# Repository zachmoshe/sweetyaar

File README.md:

# SweetYaar

SweetYaar is an ESP32-WROOM-32 baby toy audio controller. The current codebase
is a PlatformIO/Arduino C++ firmware project with:

- Bluetooth Classic A2DP speaker support.
- BLE parent controls and settings over a single-page Web Bluetooth app.
- SD-card WAV playback for songs and animal sounds.
- Configurable content metadata, sleep-mode behavior, and Bedtime mode.
- Hardware planning notes for the prototype and final PCB.

## Repository History

This repository has three useful history points:

- `main`: the current ESP32/PlatformIO firmware, Web Bluetooth parent remote,
  SD-card content template, sleep-mode work, and hardware planning artifacts.
- `v1.0`: the previous MicroPython-era implementation that used to be the
  remote `main` branch.
- `v0.0`: an older educational snapshot that used to be named `v1.0`.

To inspect the previous implementation:

```bash
git fetch origin
git switch v1.0
```

To inspect the older educational snapshot:

```bash
git switch v0.0
```

To return to the current codebase:

```bash
git switch main
```

## Development Setup

Create or refresh the root development environment:

```bash
make setup
```

The root `Makefile` is the common entry point for project tasks. Run `make help`
to list every command. The most common ones are:

```bash
make app            # Serve the parent app at http://localhost:8000/
make build          # Build the complete ESP32 firmware
make flash          # Build and upload to a connected ESP32
make monitor        # Open the serial monitor
make flash-monitor  # Flash, then monitor
make test           # Run the full regression suite
make test-unit      # Host-only tests; never flashes or touches hardware
make test-device    # Approved real-device tests (see tests/README.md)
```

Targets are intentionally thin wrappers around the component tools and can be
extended in `Makefile`. Variables can be overridden per invocation, for example
`make app APP_PORT=8080` or
`make monitor SERIAL_PORT=/dev/cu.SLAB_USBtoUART`.

## Regression Tests

Run the standard regression suite:

```bash
make test
```

The `dev` dependency group is installed by default and locked in `uv.lock`. If
the venv is activated, plain `python -m pytest` is equivalent.

See [`docs/engineering/firmware.md`](docs/engineering/firmware.md) for firmware behavior, architecture,
build instructions, and test coverage.

## Project Layout

- `firmware/esp32/`: PlatformIO project and production firmware source.
- `hardware/mainboard/`: production KiCad mainboard project and manufacturing exports.
- `hardware/debugger/`: KiCad project for the separate USB-UART debugger board.
- `hardware/libraries/`: repository-owned KiCad symbols, footprints, and 3D models.
- `hardware/mechanical/enclosure/`: enclosure STL models.
- `hardware/references/`: hardware datasheet and application-note index.
- `tests/`: host-side pytest, native C++, app, and firmware-build regression tests.
- `app/`: the deployable Web Bluetooth parent remote and editable design assets.
- `docs/engineering/`: firmware, app, and hardware engineering guides.
- `docs/assets/`: shared engineering-documentation images and diagrams.
- `content/sd-card-template/`: expected SD-card folder structure, metadata, and config.
- `tools/`: standalone utilities, including the opt-in device test runner and the WAV mono converter.
- [`docs/overview.md`](docs/overview.md): high-level project overview and design history.
- [`docs/engineering/firmware.md`](docs/engineering/firmware.md): device behavior, firmware components,
  build instructions, and regression tests.
- [`docs/engineering/mobile-app.md`](docs/engineering/mobile-app.md): parent remote behavior, design
  assets, Bedtime mode, offline support, deployment, and app tests.
- [`docs/engineering/hardware.md`](docs/engineering/hardware.md): system architecture, DevKit wiring,
  production power design, safety requirements, and bring-up checks.

## Hardware Target

The firmware targets the original ESP32-WROOM-32. This matters because the toy
uses Bluetooth Classic A2DP, which is not available on ESP32-S3/C3/C6 variants.

The current hardware plan uses GPIO13/`PERIPH_PWR_EN` as the shared active-HIGH
enable for the 3.3 V peripheral load switch and the 5 V peripheral boost. The
real app enables both branches during boot, then drives and RTC-holds GPIO13 LOW
before deep sleep; see
[`docs/engineering/hardware.md`](docs/engineering/hardware.md) for the AP2281-3WG-7 SD switch, 5 V amp
boost, required common ground, and shared-enable pulldown.

The production status indicator is a single **WS2812B-V6 (LCSC C52917433)**,
a 5050 SMD addressable RGB LED on `5V_PERIPH_SW`. GPIO2 drives `DIN` directly
through the 330 Ω `R_LED_DIN1` series resistor (LCSC C23138); the LED interface
has no MMBT3904 stage or 5 V pull-up. The `sweetyaar` environment explicitly
selects non-inverted RMT output (`SWEETYAAR_STATUS_LED_DATA_INVERTED=0`) and
24-bit GRB data (`SWEETYAAR_STATUS_LED_RGBW=0`,
`SWEETYAAR_STATUS_LED_COLOR_ORDER_GRB=1`). The `sweetyaar-generic` environment
retains the directly wired 32-bit RGBW/SK6812-style bench LED with non-inverted
data and GRBW channel order. GPIO16 and GPIO17 carry BQ25186 charger I2C SDA
and SCL, respectively. A controller-wide brightness setting scales every
available color channel and currently defaults to 50% pending enclosure testing.

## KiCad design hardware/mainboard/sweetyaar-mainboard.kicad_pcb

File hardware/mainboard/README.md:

# SweetYaar mainboard

Create the production KiCad project in this directory. Keep the project,
schematic, PCB, project library tables, and board-specific design rules together:

- `sweetyaar-mainboard.kicad_pro`
- `sweetyaar-mainboard.kicad_sch`
- `sweetyaar-mainboard.kicad_pcb`

Store immutable fabrication and assembly snapshots under `releases/<revision>/`
when a board revision is actually sent for manufacturing. Generated working
outputs belong in an ignored `fab/` directory.

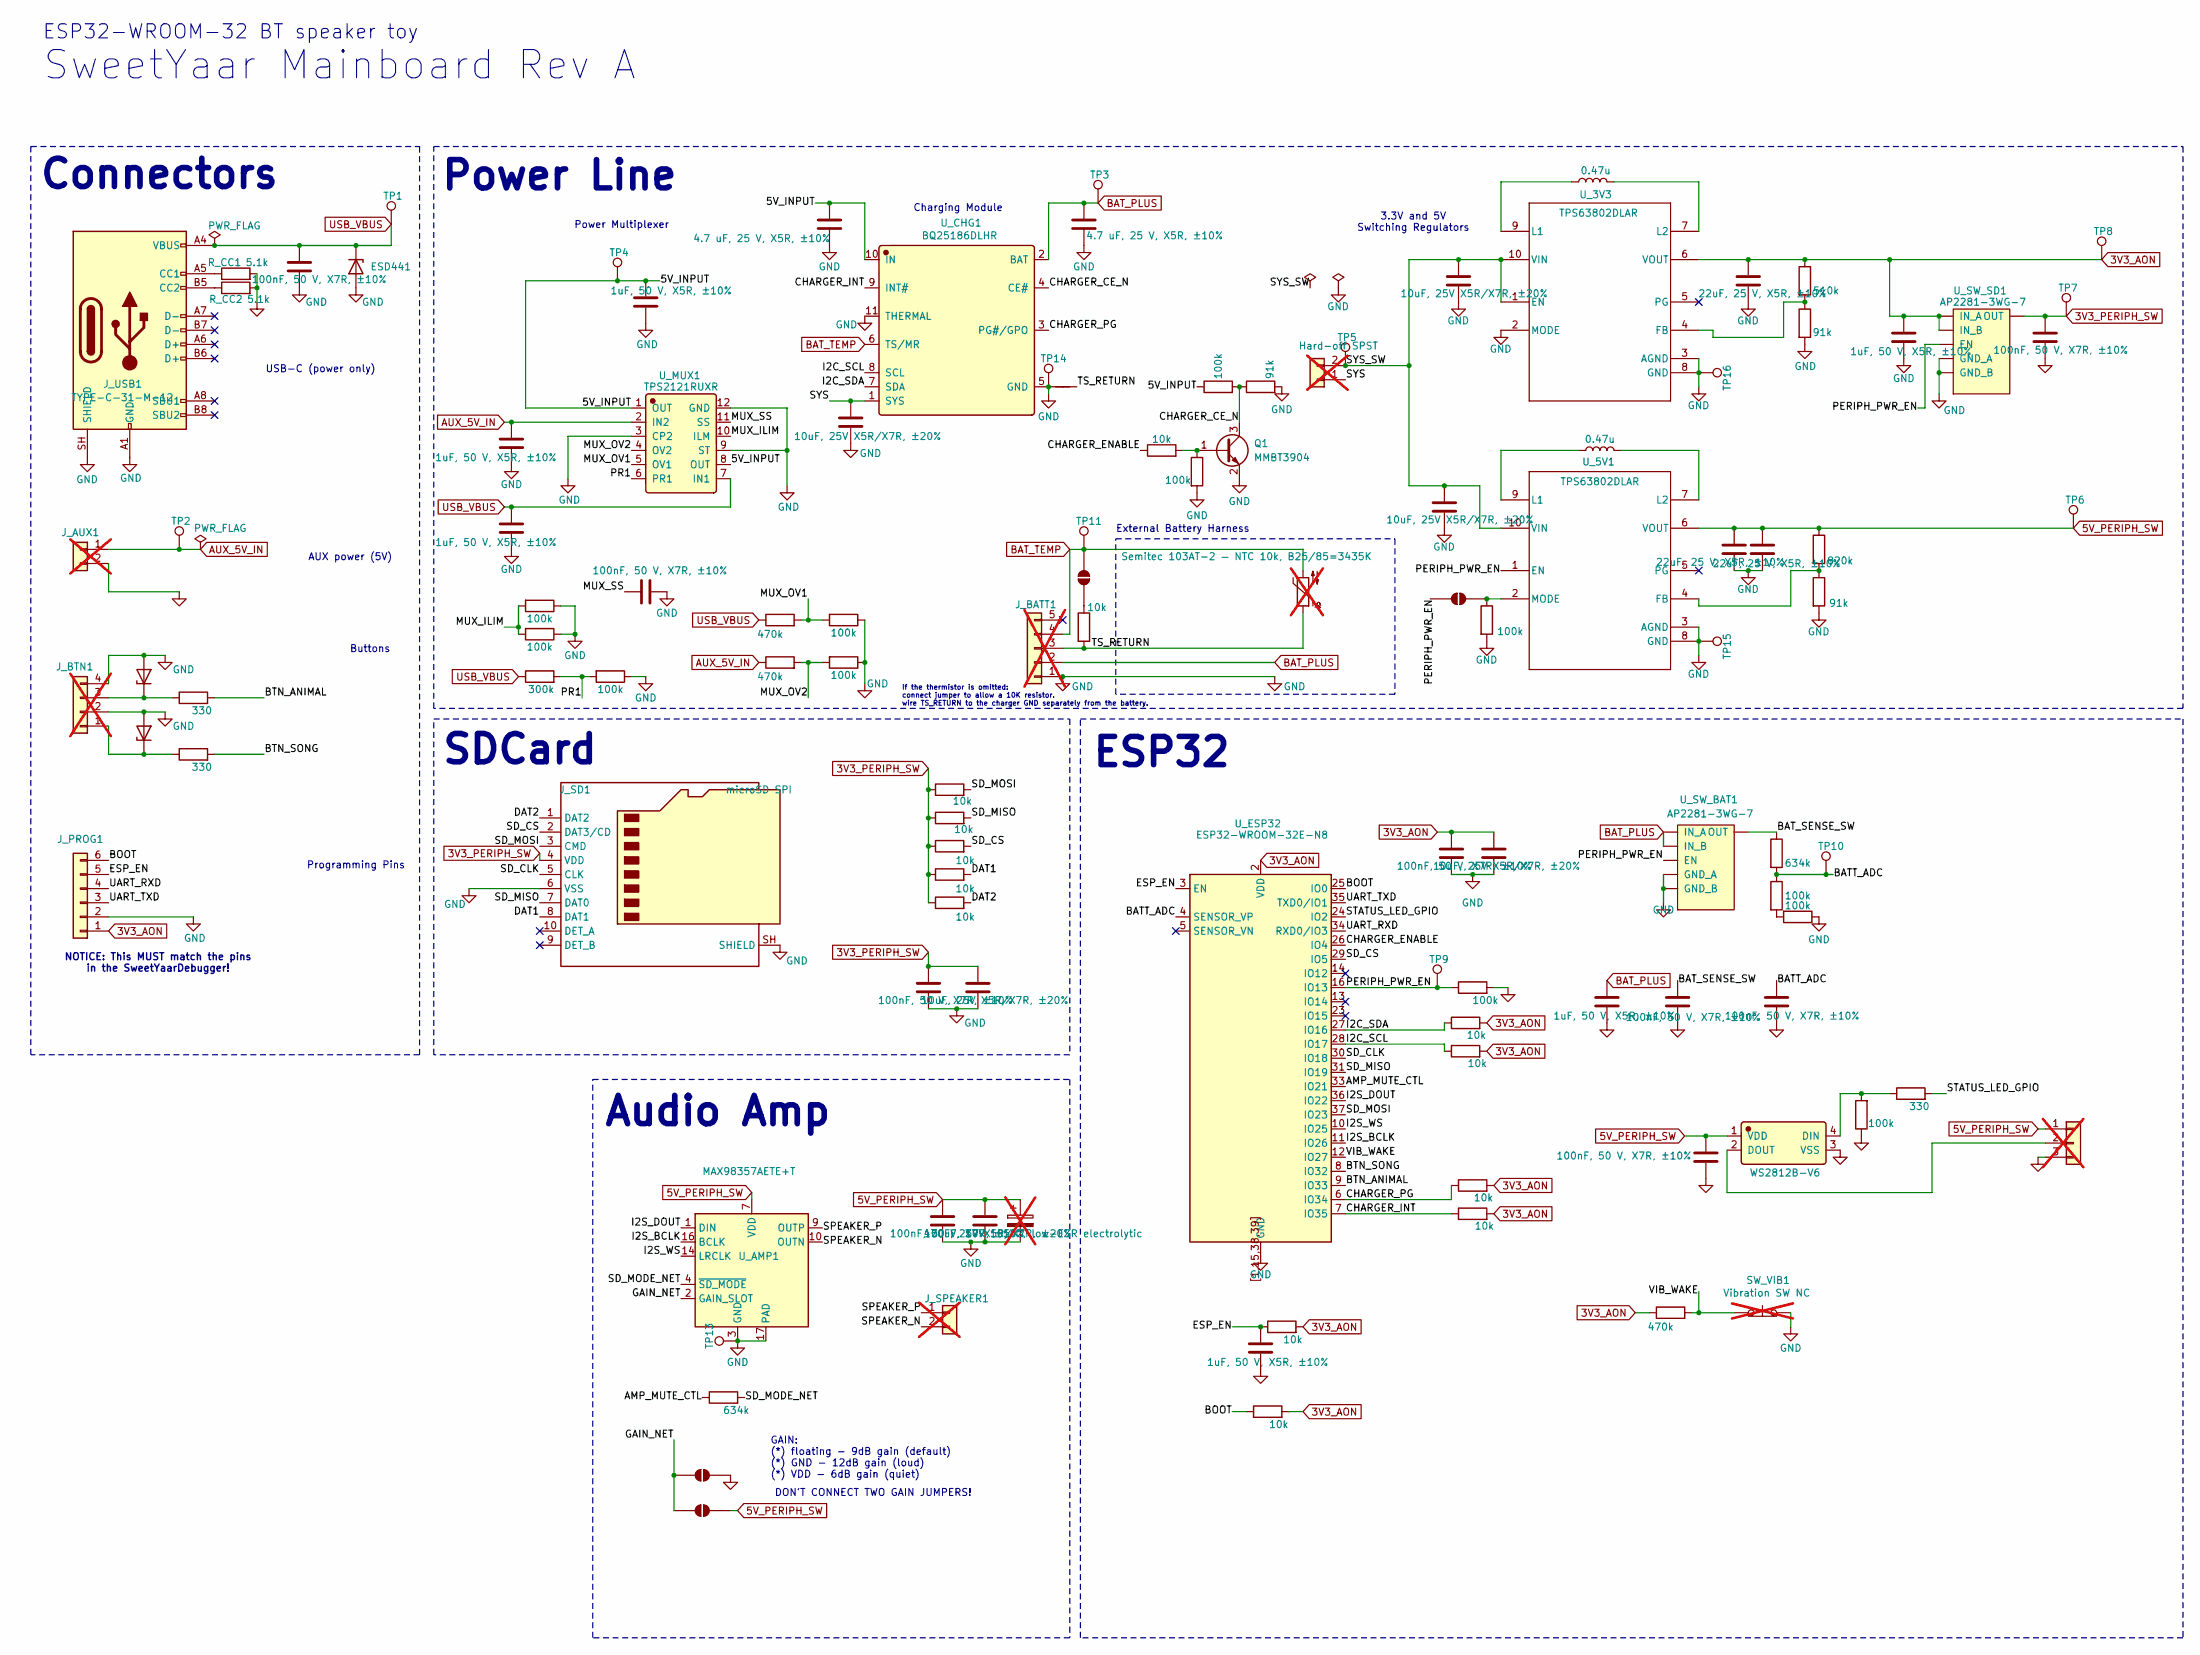
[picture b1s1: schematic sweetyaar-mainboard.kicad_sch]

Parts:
C1: 100nF, 50 V, X7R, ±10%; C_0603_1608Metric; LCSC C14663
C_3V3_IN1, C_5V_IN1: 10uF, 25V X5R/X7R, ±20%; C_0805_2012Metric; LCSC C15850
C_3V3_OUT1, C_5V_OUT1, C_5V_OUT2: 22uF, 25 V, X5R, ±10%; C_1206_3216Metric; LCSC C12891
C_AMP1: 100nF, 50 V, X7R, ±10%; C_0603_1608Metric; LCSC C14663
C_AMP2: 10uF, 25V X5R/X7R, ±20%; C_0805_2012Metric; LCSC C15850
C_AMP3: 470uF, 10V 105°C, low-ESR electrolytic; CP_Radial_D8.0mm_P3.50mm; LCSC C88765; not fitted
C_BAT_ADC1: 100nF, 50 V, X7R, ±10%; C_0603_1608Metric; LCSC C14663
C_BAT_SW_IN1: 1uF, 50 V, X5R, ±10%; C_0603_1608Metric; LCSC C15849
C_BAT_SW_OUT1: 100nF, 50 V, X7R, ±10%; C_0603_1608Metric; LCSC C14663
C_CHG_BAT1: 4.7 uF, 25 V, X5R, ±10%; C_0805_2012Metric; LCSC C1779
C_CHG_SYS1: 10uF, 25V X5R/X7R, ±20%; C_0805_2012Metric; LCSC C15850
C_ESP1: 100nF, 50 V, X7R, ±10%; C_0603_1608Metric; LCSC C14663
C_ESP2: 10uF, 25V X5R/X7R, ±20%; C_0805_2012Metric; LCSC C15850
C_ESP_EN1: 1uF, 50 V, X5R, ±10%; C_0603_1608Metric; LCSC C15849
C_LED1: 100nF, 50 V, X7R, ±10%; C_0603_1608Metric; LCSC C14663
C_MUX1, C_MUX2, C_MUX4: 1uF, 50 V, X5R, ±10%; C_0603_1608Metric; LCSC C15849
C_MUX3: 4.7 uF, 25 V, X5R, ±10%; C_0805_2012Metric; LCSC C1779
C_MUX_SS1: 100nF, 50 V, X7R, ±10%; C_0603_1608Metric; LCSC C14663
C_SD1: 100nF, 50 V, X7R, ±10%; C_0603_1608Metric; LCSC C14663
C_SD2: 10uF, 25V X5R/X7R, ±20%; C_0805_2012Metric; LCSC C15850
C_SD_SW_IN1: 1uF, 50 V, X5R, ±10%; C_0603_1608Metric; LCSC C15849
C_SD_SW_OUT1: 100nF, 50 V, X7R, ±10%; C_0603_1608Metric; LCSC C14663
D1, D3, D5: ESD441; Texas_DPY0002A_0.6x1mm_P0.65mm; LCSC C53161160
D_LED1: WS2812B-V6; Manufacturer Part WS2812B-V6; LCSC C52917433
JP1, JP2, JP3, JP4: SolderJumper_2_Open; SolderJumper-2_P1.3mm_Open_RoundedPad1.0x1.5mm; LCSC N/A
J_AUX1: AUX_5V_IN; JST_XH_B2B-XH-A_1x02_P2.50mm_Vertical; LCSC C158012; not fitted
J_BATT1: BAT JST-XH; JST_XH_B5B-XH-A_1x05_P2.50mm_Vertical; not fitted
J_BTN1: BUTTONS; JST_XH_B4B-XH-A_1x04_P2.50mm_Vertical; LCSC C144395; not fitted
J_LED_EXT1: Conn_01x03; JST_XH_B3B-XH-A_1x03_P2.50mm_Vertical; LCSC C144394; not fitted
J_PROG1: PROG_HDR; DebuggerPad_1x06_P2.54mm; LCSC N/A
J_SD1: microSD SPI; microSD_HC_Molex_104031-0811; LCSC C585350
J_SPEAKER1: SPEAKER; JST_XH_B2B-XH-A_1x02_P2.50mm_Vertical; LCSC C158012; not fitted
J_SWITCH1: Hard-off SPST; JST_XH_B2B-XH-A_1x02_P2.50mm_Vertical; LCSC C158012; not fitted
J_USB1: TYPE-C-31-M-12; USB_C_Receptacle_HRO_TYPE-C-31-M-12 - C165948; LCSC C165948
L_3V3, L_5V1: 0.47u; L_Murata_DFE201612E; LCSC C668312
NT1: NetTie_2; NetTie-2_SMD_Pad0.5mm
Q1: MMBT3904; SOT-23; LCSC C20526
R_3V3_BOT1, R_5V_BOT1: 91k; R_0603_1608Metric; LCSC C23265
R_3V3_TOP1: 510k; R_0603_1608Metric; LCSC C23192
R_5V_EN_PD1: 100k; R_0603_1608Metric; LCSC C25803
R_5V_TOP1: 820k; R_0603_1608Metric; LCSC C23252
R_BAT_H1: 634k; R_0603_1608Metric; LCSC C65831
R_BAT_L1, R_BAT_L2: 100k; R_0603_1608Metric; LCSC C25803
R_BOOT_PULLUP1: 10k; R_0603_1608Metric; LCSC C25804
R_BTN_ANIMAL1: 330; R_0603_1608Metric; LCSC C23138
R_BTN_SONG1: 330; R_0603_1608Metric; LCSC C23138
R_CC1, R_CC2: 5.1k; R_0603_1608Metric; LCSC C23186
R_CHARGER_CE_BASE1: 10k; R_0603_1608Metric; LCSC C25804
R_CHARGER_CE_DIV1: 100k; R_0603_1608Metric; LCSC C25803
R_CHARGER_CE_DIV2: 91k; R_0603_1608Metric; LCSC C23265
R_CHARGER_CE_PD1: 100k; R_0603_1608Metric; LCSC C25803
R_ESP_EN_PULLUP1: 10k; R_0603_1608Metric; LCSC C25804
R_INT1: 10k; R_0603_1608Metric; LCSC C25804
R_LED_DIN1: 330; R_0603_1608Metric; LCSC C23138
R_LED_DIN2: 100k; R_0603_1608Metric; LCSC C25803
R_MODE_PD1: 100k; R_0603_1608Metric; LCSC C25803
R_MUX_ILIM1, R_MUX_ILIM2: 100k; R_0603_1608Metric; LCSC C25803
R_MUX_OV_DIV1, R_MUX_OV_DIV3: 470k; R_0603_1608Metric; LCSC C23178
R_MUX_OV_DIV2, R_MUX_OV_DIV4: 100k; R_0603_1608Metric; LCSC C25803
R_PG1: 10k; R_0603_1608Metric; LCSC C25804
R_PR1_BOT1: 100k; R_0603_1608Metric; LCSC C25803
R_PR1_TOP1: 300k; R_0603_1608Metric; LCSC C23024
R_SCL1: 10k; R_0603_1608Metric; LCSC C25804
R_SDA1: 10k; R_0603_1608Metric; LCSC C25804
R_SDMODE1: 634k; R_0603_1608Metric; LCSC C65831
R_SD_CS1: 10k; R_0603_1608Metric; LCSC C25804
R_SD_DAT1, R_SD_DAT2: 10k; R_0603_1608Metric; LCSC C25804
R_SD_MISO1: 10k; R_0603_1608Metric; LCSC C25804
R_SD_MOSI1: 10k; R_0603_1608Metric; LCSC C25804
R_TH1: 10k; R_0603_1608Metric; LCSC C25804
R_VIB1: 470k; R_0603_1608Metric; LCSC C23178
SW_VIB1: Vibration SW NC; R_Axial_DIN0516_L15.5mm_D5.0mm_P20.32mm_Horizontal; LCSC N/A; not fitted
TH1: Semitec 103AT-2 — NTC 10k, B25/85=3435K; LCSC N/A; not fitted
TP1, TP2, TP3, TP4, TP5, TP6, TP7, TP8, TP9, TP10, TP11, TP13, TP14, TP15, TP16: ${SHORT_NET_NAME(1)}; TestPoint_Pad_D2.0mm
U_3V3, U_5V1: TPS63802DLAR; DLA0010A; LCSC C2845237
U_AMP1: MAX98357AETE+T; TQFN-16-1EP_3x3mm_P0.5mm_EP1.23x1.23mm - C910544; LCSC C910544
U_CHG1: BQ25186DLHR; Texas_DLH0010A_WSON-10-1EP_2.2x2mm_P0.4mm_EP0.9x1.5mm; Manufacturer Part BQ25186DLHR; LCSC C44639442
U_ESP32: ESP32-WROOM-32E-N8; ESP32-WROOM-32E - C701342; LCSC C701342
U_MUX1: TPS2121RUXR; Texas_VQFN-HR-12_2x2.5mm_P0.5mm; Manufacturer Part TPS2121RUXR; LCSC C485916
U_SW_BAT1: AP2281-3WG-7; SOT-23-6 - C128634; LCSC C128634
U_SW_SD1: AP2281-3WG-7; SOT-23-6 - C128634; LCSC C128634

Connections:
3V3_AON: C_3V3_OUT1.1, C_ESP1.1, C_ESP2.1, C_SD_SW_IN1.1, J_PROG1.1, R_3V3_TOP1.1, R_BOOT_PULLUP1.2, R_ESP_EN_PULLUP1.2, R_INT1.2, R_PG1.2, R_SCL1.2, R_SDA1.2, R_VIB1.1, TP8.1 (1_1), U_3V3.6 (VOUT), U_ESP32.2 (VDD), U_SW_SD1.4 (IN_A), U_SW_SD1.6 (IN_B)
3V3_PERIPH_SW: C_SD1.1, C_SD2.1, C_SD_SW_OUT1.1, J_SD1.4 (VDD), R_SD_CS1.1, R_SD_DAT1.1, R_SD_DAT2.1, R_SD_MISO1.1, R_SD_MOSI1.1, TP7.1 (1_1), U_SW_SD1.1 (OUT)
5V_PERIPH_SW: C_5V_OUT1.1, C_5V_OUT2.1, C_AMP1.1, C_AMP2.1, C_AMP3.1, C_LED1.1, D_LED1.1 (VDD), JP2.2 (B), J_LED_EXT1.1, R_5V_TOP1.1, TP6.1 (1_1), U_5V1.6 (VOUT), U_AMP1.7 (VDD), U_AMP1.8 (VDD)
/5V_INPUT: C_MUX3.1, C_MUX4.1, R_CHARGER_CE_DIV1.1, TP4.1 (1_1), U_CHG1.10 (IN), U_MUX1.1 (OUT), U_MUX1.8 (OUT)
/AMP_MUTE_CTL: R_SDMODE1.1, U_ESP32.33 (IO21)
/BATT_ADC: C_BAT_ADC1.1, R_BAT_H1.2, R_BAT_L1.1, TP10.1 (1_1), U_ESP32.4 (SENSOR_VP)
/BAT_SENSE_SW: C_BAT_SW_OUT1.1, R_BAT_H1.1, U_SW_BAT1.1 (OUT)
/BOOT: J_PROG1.6, R_BOOT_PULLUP1.1, U_ESP32.25 (IO0)
/BTN_ANIMAL: R_BTN_ANIMAL1.2, U_ESP32.9 (IO33)
/BTN_SONG: R_BTN_SONG1.2, U_ESP32.8 (IO32)
/CHARGER_CE_N: Q1.3 (C), R_CHARGER_CE_DIV1.2, R_CHARGER_CE_DIV2.1, U_CHG1.4 (CE#)
/CHARGER_ENABLE: R_CHARGER_CE_BASE1.1, U_ESP32.26 (IO4)
/CHARGER_INT: R_INT1.1, U_CHG1.9 (INT#), U_ESP32.7 (IO35)
/CHARGER_PG: R_PG1.1, U_CHG1.3 (PG#/GPO), U_ESP32.6 (IO34)
/DAT1: J_SD1.8 (DAT1), R_SD_DAT1.2
/DAT2: J_SD1.1 (DAT2), R_SD_DAT2.2
/ESP_EN: C_ESP_EN1.1, J_PROG1.5, R_ESP_EN_PULLUP1.1, U_ESP32.3 (EN)
/GAIN_NET: JP1.1 (A), JP2.1 (A), U_AMP1.2 (GAIN_SLOT)
/I2C_SCL: R_SCL1.1, U_CHG1.8 (SCL), U_ESP32.28 (IO17)
/I2C_SDA: R_SDA1.1, U_CHG1.7 (SDA), U_ESP32.27 (IO16)
/I2S_BCLK: U_AMP1.16 (BCLK), U_ESP32.11 (IO26)
/I2S_DOUT: U_AMP1.1 (DIN), U_ESP32.36 (IO22)
/I2S_WS: U_AMP1.14 (LRCLK), U_ESP32.10 (IO25)
/MUX_ILIM: R_MUX_ILIM1.2, R_MUX_ILIM2.2, U_MUX1.10 (ILM)
/MUX_OV1: R_MUX_OV_DIV1.2, R_MUX_OV_DIV2.2, U_MUX1.5 (OV1)
/MUX_OV2: R_MUX_OV_DIV3.2, R_MUX_OV_DIV4.2, U_MUX1.4 (OV2)
/MUX_SS: C_MUX_SS1.2, U_MUX1.11 (SS)
/PERIPH_PWR_EN: JP4.1 (A), R_5V_EN_PD1.1, TP9.1 (1_1), U_5V1.1 (EN), U_ESP32.16 (IO13), U_SW_BAT1.3 (EN), U_SW_SD1.3 (EN)
/PR1: R_PR1_BOT1.2, R_PR1_TOP1.2, U_MUX1.6 (PR1)
/SD_CLK: J_SD1.5 (CLK), U_ESP32.30 (IO18)
/SD_CS: J_SD1.2 (DAT3/CD), R_SD_CS1.2, U_ESP32.29 (IO5)
/SD_MISO: J_SD1.7 (DAT0), R_SD_MISO1.2, U_ESP32.31 (IO19)
/SD_MODE_NET: R_SDMODE1.2, U_AMP1.4 (~SD_MODE)
/SD_MOSI: J_SD1.3 (CMD), R_SD_MOSI1.2, U_ESP32.37 (IO23)
/SPEAKER_N: J_SPEAKER1.2, U_AMP1.10 (OUTN)
/SPEAKER_P: J_SPEAKER1.1, U_AMP1.9 (OUTP)
/STATUS_LED_GPIO: R_LED_DIN1.2, U_ESP32.24 (IO2)
/SYS: C_CHG_SYS1.1, J_SWITCH1.1, U_CHG1.1 (SYS)
/SYS_SW: C_3V3_IN1.1, C_5V_IN1.1, J_SWITCH1.2, TP5.1 (1_1), U_3V3.1 (EN), U_3V3.10 (VIN), U_5V1.10 (VIN)
/TS_RETURN: J_BATT1.3, NT1.2, R_TH1.2, TH1.1
/UART_RXD: J_PROG1.4, U_ESP32.34 (RXD0/IO3)
/UART_TXD: J_PROG1.3, U_ESP32.35 (TXD0/IO1)
/VIB_WAKE: R_VIB1.2, SW_VIB1.1 (A), U_ESP32.12 (IO27)
AUX_5V_IN: C_MUX2.1, J_AUX1.1, R_MUX_OV_DIV3.1, TP2.1 (1_1), U_MUX1.2 (IN2)
BAT_PLUS: C_BAT_SW_IN1.1, C_CHG_BAT1.1, J_BATT1.2, TP3.1 (1_1), U_CHG1.2 (BAT), U_SW_BAT1.4 (IN_A), U_SW_BAT1.6 (IN_B)
BAT_TEMP: JP3.2 (B), J_BATT1.4, TH1.2, TP11.1 (1_1), U_CHG1.6 (TS/MR)
GND: C1.1, C_3V3_IN1.2, C_3V3_OUT1.2, C_5V_IN1.2, C_5V_OUT1.2, C_5V_OUT2.2, C_AMP1.2, C_AMP2.2, C_AMP3.2, C_BAT_ADC1.2, C_BAT_SW_IN1.2, C_BAT_SW_OUT1.2, C_CHG_BAT1.2, C_CHG_SYS1.2, C_ESP1.2, C_ESP2.2, C_ESP_EN1.2, C_LED1.2, C_MUX1.2, C_MUX2.2, C_MUX3.2, C_MUX4.2, C_MUX_SS1.1, C_SD1.2, C_SD2.2, C_SD_SW_IN1.2, C_SD_SW_OUT1.2, D1.2 (A), D3.2 (A), D5.2 (A), D_LED1.3 (VSS), JP1.2 (B), J_AUX1.2, J_BATT1.1, J_BTN1.2, J_BTN1.4, J_LED_EXT1.3, J_PROG1.2, J_SD1.6 (VSS), J_SD1.SH (SHIELD), J_USB1.A1 (GND), J_USB1.A12 (GND), J_USB1.B1 (GND), J_USB1.B12 (GND), J_USB1.SH (SHIELD), NT1.1, Q1.2 (E), R_3V3_BOT1.2, R_5V_BOT1.2, R_5V_EN_PD1.2, R_BAT_L2.1, R_CC1.2, R_CC2.2, R_CHARGER_CE_DIV2.2, R_CHARGER_CE_PD1.2, R_LED_DIN2.1, R_MODE_PD1.2, R_MUX_ILIM1.1, R_MUX_ILIM2.1, R_MUX_OV_DIV2.1, R_MUX_OV_DIV4.1, R_PR1_BOT1.1, SW_VIB1.2 (B), TP13.1 (1_1), TP14.1 (1_1), TP15.1 (1_1), TP16.1 (1_1), U_3V3.2 (MODE), U_3V3.3 (AGND), U_3V3.8 (GND), U_5V1.3 (AGND), U_5V1.8 (GND), U_AMP1.3 (GND), U_AMP1.11 (GND), U_AMP1.15 (GND), U_AMP1.17 (PAD), U_CHG1.5 (GND), U_CHG1.11 (THERMAL), U_ESP32.1 (GND), U_ESP32.15 (GND), U_ESP32.38 (GND), U_ESP32.39 (GND), U_ESP32.[1,15,38,39] (GND), U_MUX1.3 (CP2), U_MUX1.9 (ST), U_MUX1.12 (GND), U_SW_BAT1.2 (GND_A), U_SW_BAT1.5 (GND_B), U_SW_SD1.2 (GND_A), U_SW_SD1.5 (GND_B)
unnamed: D3.1 (K), J_BTN1.1, R_BTN_SONG1.1
unnamed: D5.1 (K), J_BTN1.3, R_BTN_ANIMAL1.1
unnamed: D_LED1.4 (DIN), R_LED_DIN1.1, R_LED_DIN2.2
unnamed: D_LED1.2 (DOUT), J_LED_EXT1.2
unnamed: JP3.1 (A), R_TH1.1
unnamed: JP4.2 (B), R_MODE_PD1.1, U_5V1.2 (MODE)
unnamed: J_USB1.A5 (CC1), R_CC1.1
unnamed: J_USB1.B5 (CC2), R_CC2.1
unnamed: Q1.1 (B), R_CHARGER_CE_BASE1.2, R_CHARGER_CE_PD1.1
unnamed: R_BAT_L1.2, R_BAT_L2.2
unnamed: R_3V3_BOT1.1, R_3V3_TOP1.2, U_3V3.4 (FB)
unnamed: L_3V3.1, U_3V3.9 (L1)
unnamed: L_3V3.2, U_3V3.7 (L2)
unnamed: R_5V_BOT1.1, R_5V_TOP1.2, U_5V1.4 (FB)
unnamed: L_5V1.1, U_5V1.9 (L1)
unnamed: L_5V1.2, U_5V1.7 (L2)
USB_VBUS: C1.2, C_MUX1.1, D1.1 (K), J_USB1.A4 (VBUS), J_USB1.A9 (VBUS), J_USB1.B4 (VBUS), J_USB1.B9 (VBUS), R_MUX_OV_DIV1.1, R_PR1_TOP1.1, TP1.1 (1_1), U_MUX1.7 (IN1)

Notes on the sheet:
AUX power (5V)
Programming Pins
NOTICE: This MUST match the pins in the SweetYaarDebugger!
GAIN: (*) floating - 9dB gain (default) (*) GND - 12dB gain (loud) (*) VDD - 6dB gain (quiet)
Connectors
USB-C (power only)
SDCard
Buttons
If the thermistor is omitted: connect jumper to allow a 10K resistor. wire TS_RETURN to the charger GND separately from the battery.
Power Line
SweetYaar Mainboard Rev A
ESP32-WROOM-32 BT speaker toy
3.3V and 5V Switching Regulators
Power Multiplexer
Audio Amp
Charging Module
ESP32
DON'T CONNECT TWO GAIN JUMPERS!
External Battery Harness

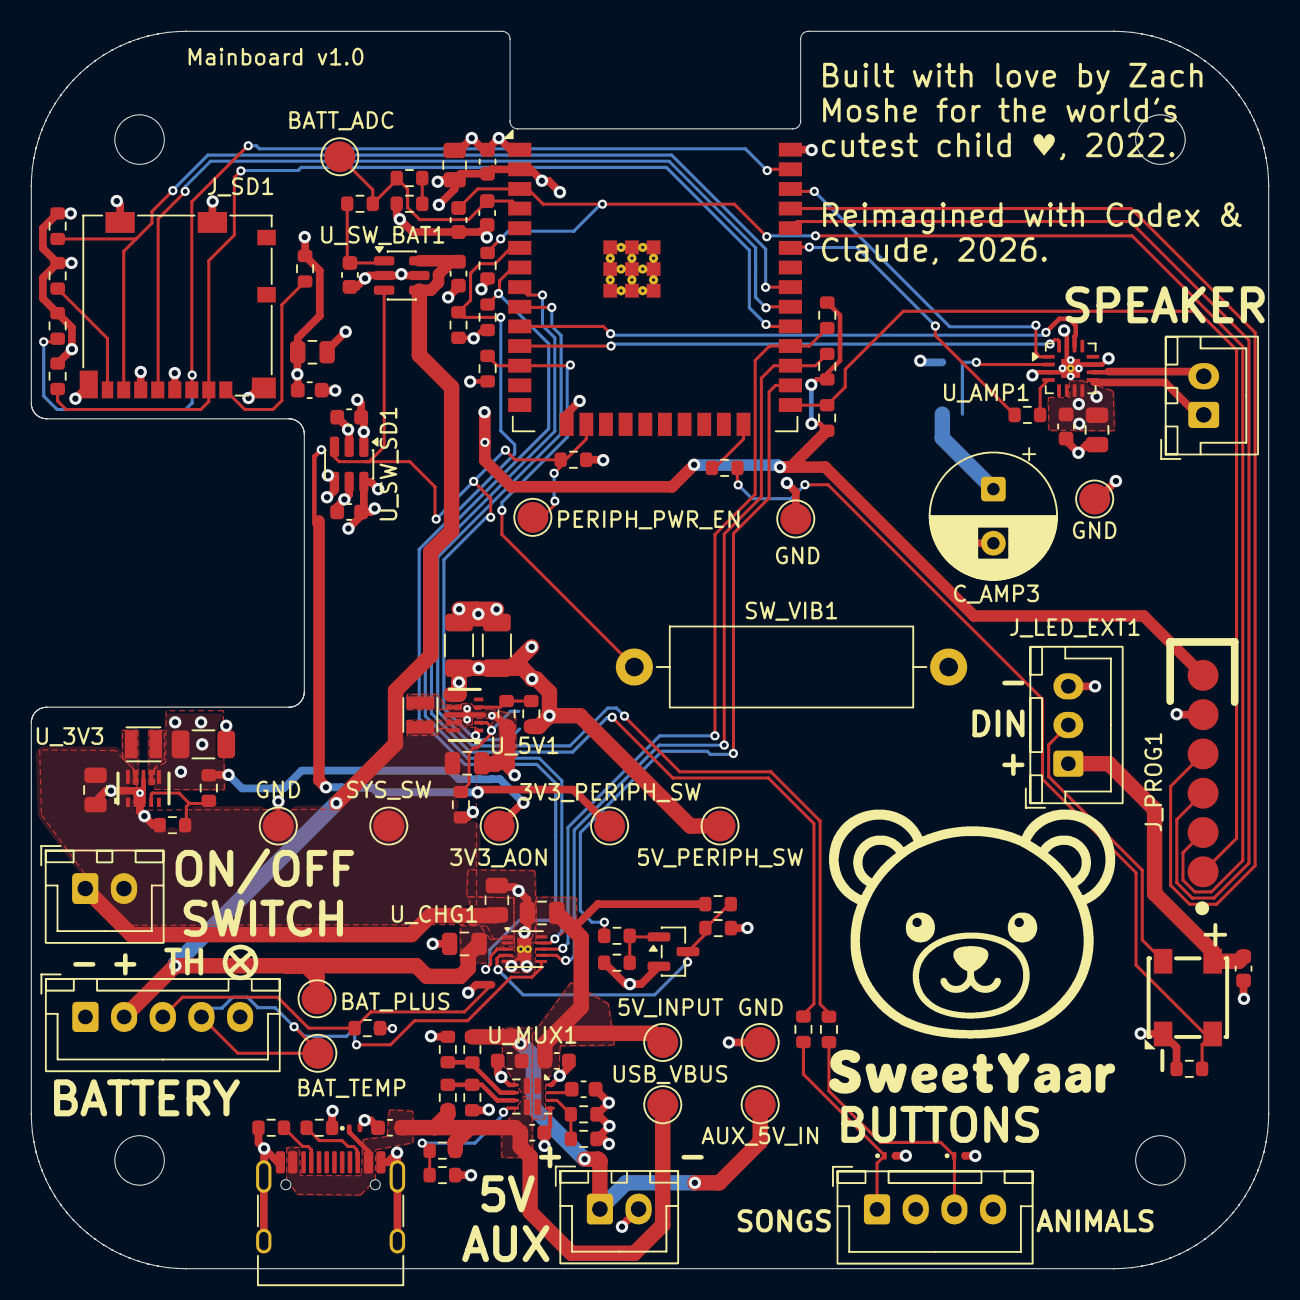
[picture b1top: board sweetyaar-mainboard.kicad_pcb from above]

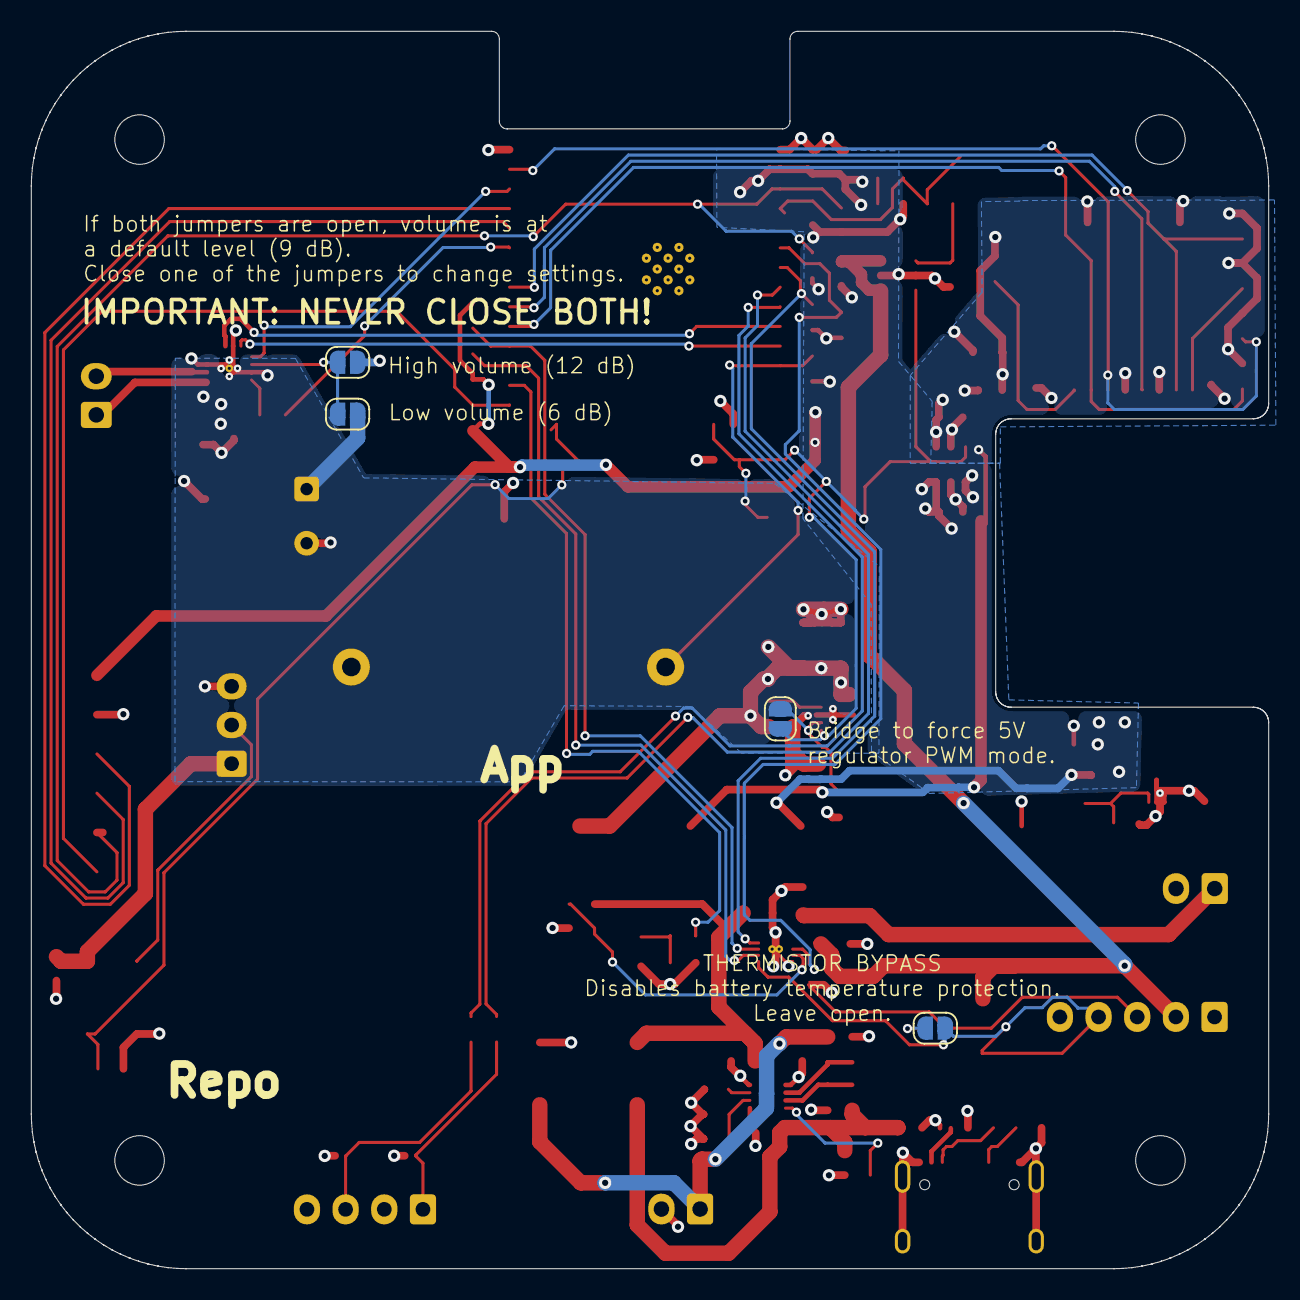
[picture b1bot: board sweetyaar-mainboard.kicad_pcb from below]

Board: 4 copper layers, 80.0 x 80.0 mm, 114 parts (4 on the bottom side), 64 nets.

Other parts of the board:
LOGO: Logo_SweetYaar_Teddy_20x20mm

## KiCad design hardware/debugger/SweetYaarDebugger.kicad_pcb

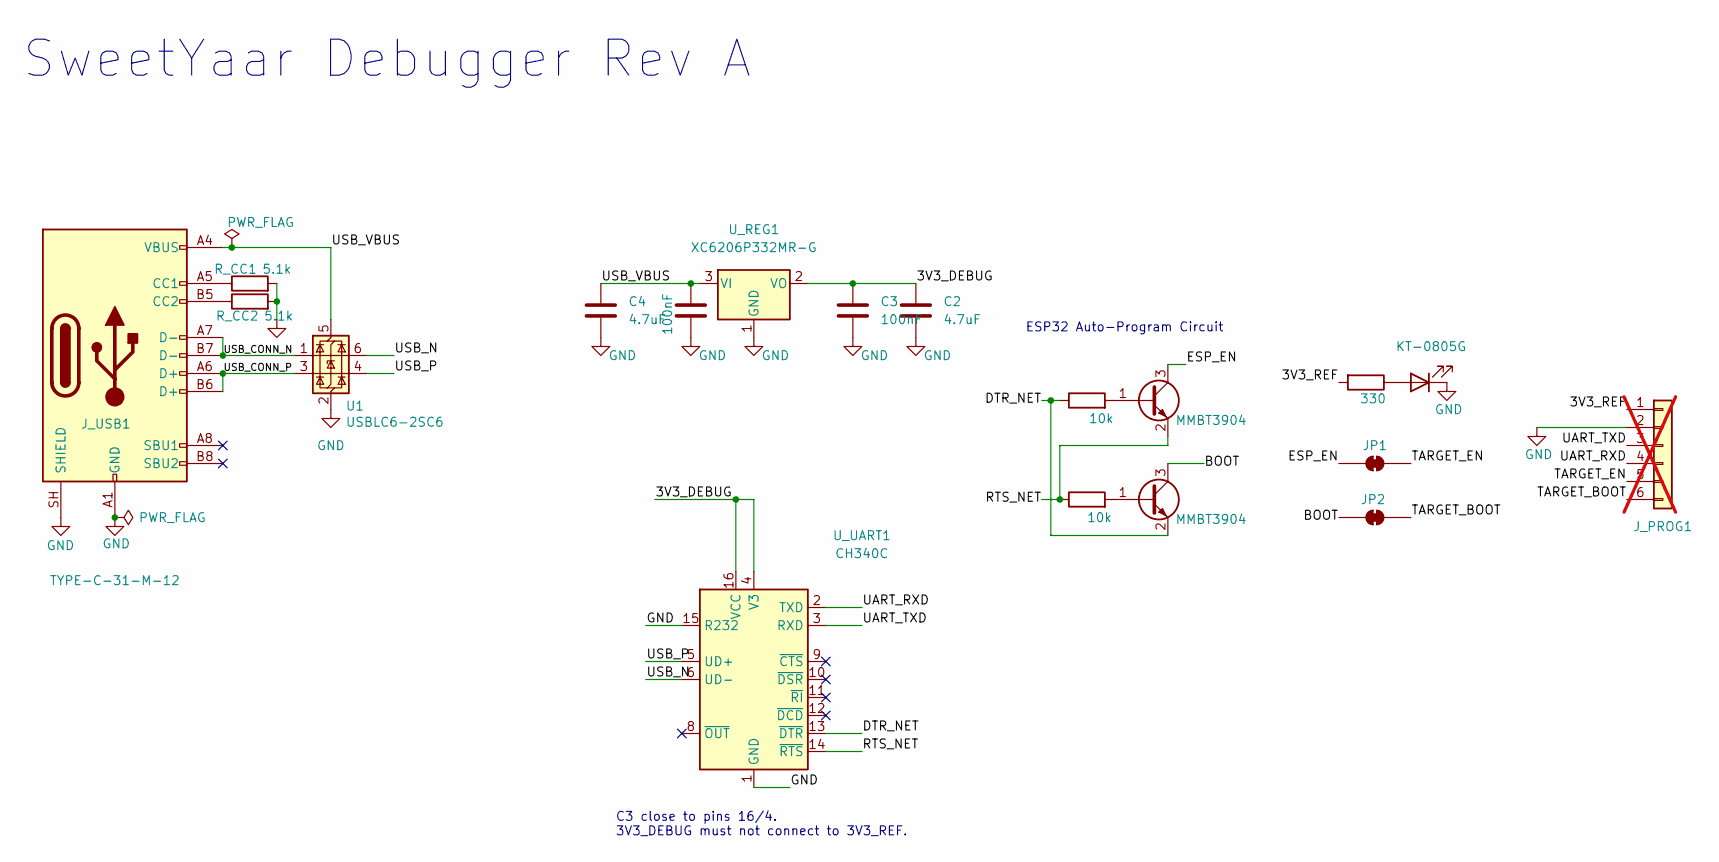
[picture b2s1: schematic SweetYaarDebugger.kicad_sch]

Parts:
C1, C3: 100nF; C_0603_1608Metric; LCSC C14663
C2, C4: 4.7uF; C_0805_2012Metric; LCSC C1779
D1: KT-0805G; LED_0805_2012Metric; LCSC C2297
JP1, JP2: SolderJumper_2_Bridged; SolderJumper-2_P1.3mm_Bridged_RoundedPad1.0x1.5mm
J_PROG1: PROG_HDR; PinHeader_1x06_P2.54mm_Vertical; not fitted
J_USB1: TYPE-C-31-M-12; USB_C_Receptacle_HRO_TYPE-C-31-M-12 - C165948; LCSC C165948
Q_DTR1: MMBT3904; SOT-23; LCSC C20526
Q_RTS1: MMBT3904; SOT-23; LCSC C20526
R1: 330; R_0603_1608Metric; LCSC C23138
R_CC1, R_CC2: 5.1k; R_0603_1608Metric; LCSC C23186
R_DTR1: 10k; R_0603_1608Metric; LCSC C25804
R_RTS1: 10k; R_0603_1608Metric; LCSC C25804
U1: USBLC6-2SC6; SOT-23-6 - USBLC6-2SC6 - C7519; LCSC C7519
U_REG1: XC6206P332MR-G; SOT-23-3; LCSC C5446
U_UART1: CH340C; SOIC-16_3.9x9.9mm_P1.27mm; LCSC C7464026

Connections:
/3V3_DEBUG: C2.1, C3.1, U_REG1.2 (VO), U_UART1.4 (V3), U_UART1.16 (VCC)
/3V3_REF: J_PROG1.1, R1.2
/BOOT: JP2.1 (A), Q_RTS1.3 (C)
/DTR_NET: Q_RTS1.2 (E), R_DTR1.1, U_UART1.13 (~DTR)
/ESP_EN: JP1.1 (A), Q_DTR1.3 (C)
/RTS_NET: Q_DTR1.2 (E), R_RTS1.1, U_UART1.14 (~RTS)
/TARGET_BOOT: JP2.2 (B), J_PROG1.6
/TARGET_EN: JP1.2 (B), J_PROG1.5
/UART_RXD: J_PROG1.4, U_UART1.2 (TXD)
/UART_TXD: J_PROG1.3, U_UART1.3 (RXD)
/USB_CONN_N: J_USB1.A7 (D-), J_USB1.B7 (D-), U1.1 (I/O1)
/USB_CONN_P: J_USB1.A6 (D+), J_USB1.B6 (D+), U1.3 (I/O2)
/USB_N: U1.6 (I/O1), U_UART1.6 (UD-)
/USB_P: U1.4 (I/O2), U_UART1.5 (UD+)
/USB_VBUS: C1.2, C4.1, J_USB1.A4 (VBUS), J_USB1.A9 (VBUS), J_USB1.B4 (VBUS), J_USB1.B9 (VBUS), U1.5 (VBUS), U_REG1.3 (VI)
GND: C1.1, C2.2, C3.2, C4.2, D1.1 (K), J_PROG1.2, J_USB1.A1 (GND), J_USB1.A12 (GND), J_USB1.B1 (GND), J_USB1.B12 (GND), J_USB1.SH (SHIELD), R_CC1.2, R_CC2.2, U1.2 (GND), U_REG1.1 (GND), U_UART1.1 (GND), U_UART1.15 (R232)
unnamed: D1.2 (A), R1.1
unnamed: J_USB1.A5 (CC1), R_CC1.1
unnamed: J_USB1.B5 (CC2), R_CC2.1
unnamed: Q_DTR1.1 (B), R_DTR1.2
unnamed: Q_RTS1.1 (B), R_RTS1.2

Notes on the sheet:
SweetYaar Debugger Rev A
C3 close to pins 16/4. 3V3_DEBUG must not connect to 3V3_REF.
ESP32 Auto-Program Circuit

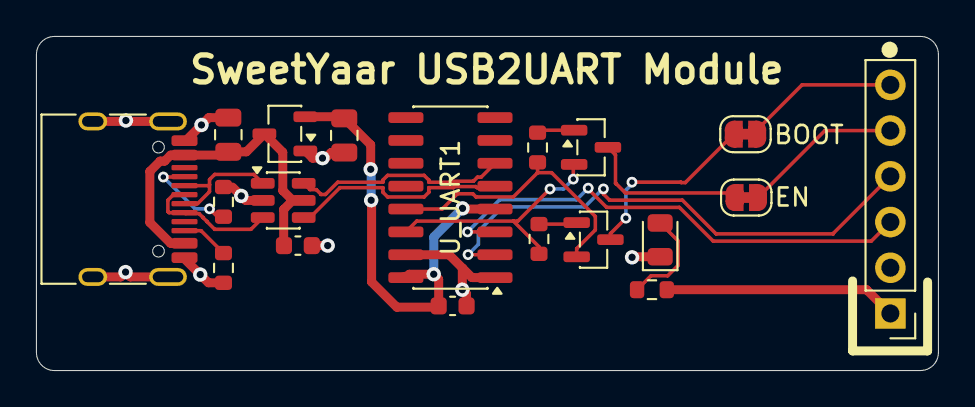
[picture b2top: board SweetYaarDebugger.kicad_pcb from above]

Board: 2 copper layers, 50.1 x 18.6 mm, 19 parts (0 on the bottom side), 21 nets.

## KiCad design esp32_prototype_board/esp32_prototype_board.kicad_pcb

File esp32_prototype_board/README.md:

# ESP32 Prototype Board Rev A

This folder tracks the first reusable PCB concept for ESP32 audio/storage experiments.
The goal is not to make the smallest possible product board. The goal is to make a
stable lab board that removes breadboard pain for projects using Bluetooth, SD cards,
I2S audio, USB serial programming, external 5V power, and spare GPIO.

## What To Install

Start with these tools:

1. **KiCad** for schematic and PCB layout.
   Download from <https://www.kicad.org/download/>.

2. **Espressif KiCad libraries** are optional for this Rev A. KiCad 10 already
   includes `RF_Module:ESP32-WROOM-32E`, which is enough to start.

3. **JLCPCB KiCad tools** later, after the schematic and PCB are real.
   Plugin repository: <https://github.com/Bouni/kicad-jlcpcb-tools>.

You do not need to install manufacturing tools yet. First we will design and review
the board in KiCad. After that, we will generate Gerbers, BOM, and CPL/position files.

## Rev A Philosophy

- Use one-sided SMT assembly on the top side only.
- Prefer JLCPCB Basic parts where practical.
- Avoid BGA packages entirely.
- Avoid QFN packages unless there is no reasonable alternative.
- Use an ESP32-WROOM-32E module instead of a bare ESP32 chip.
- Place the ESP32 module antenna at the edge of the board with the required keepout.
- Keep the board comfortable and labeled, not tiny.
- Hand-solder bulky connectors and headers if that reduces assembly cost.

## Current Rev A Defaults

The current decisions are recorded in [rev-a-decisions.md](rev-a-decisions.md).
The component starting points are recorded in
[component-defaults.md](component-defaults.md). The rough small-run cost estimate is
in [cost-estimate.md](cost-estimate.md). The work plan from here is in
[next-steps.md](next-steps.md).

The current schematic status and verification notes are in
[schematic-status.md](schematic-status.md).
The current first PCB placement preview is in
[placement-preview.svg](placement-preview.svg), generated from
`tools/generate_initial_pcb.py`.
Connector/header meanings are explained in
[connectors-explained.md](connectors-explained.md).
For continuing this work in a fresh chat, start with
[fresh-chat-brief.md](fresh-chat-brief.md).

## Major Blocks

- ESP32-WROOM-32E module with built-in PCB antenna.
- USB-C connector for 5V power and USB serial data.
- USB-UART bridge for programming and serial monitor.
- External 5V input terminal for bench PSU power.
- Simple power-source selection so external 5V cannot backfeed USB.
- 3.3V regulator for ESP32, SD card, and logic.
- Soldered microSD socket wired in SPI mode.
- Soldered MAX98357A breakout header with mute control.
- Speaker connection directly on the MAX98357A module.
- I2C expansion header.
- SPI expansion header sharing the SD SPI bus.
- Spare GPIO headers with power and ground nearby.
- SweetYaar sleep-mode add-on support through headers: GPIO27 for passive
  vibration wake and GPIO13 for active-HIGH peripheral load-switch enable.
- Test pads for important rails and buses.

## Open Rev A Decisions

- Route the first PCB placement.
- Resolve the KiCad CLI DRC abort around the USB-C/J1 footprint, or confirm it is
  CLI-only by running DRC in the KiCad GUI.
- Final board dimensions after routing review.

## Useful References

- KiCad downloads: <https://www.kicad.org/download/>
- Espressif KiCad libraries: <https://github.com/espressif/kicad-libraries>
- ESP32-WROOM-32E/32UE datasheet: <https://documentation.espressif.com/esp32-wroom-32e_esp32-wroom-32ue_datasheet_en.html>
- ESP32 PCB layout guidelines: <https://docs.espressif.com/projects/esp-hardware-design-guidelines/en/latest/esp32/pcb-layout-design.html>
- ESP-IDF SD pull-up requirements: <https://docs.espressif.com/projects/esp-idf/en/stable/esp32/api-reference/peripherals/sd_pullup_requirements.html>

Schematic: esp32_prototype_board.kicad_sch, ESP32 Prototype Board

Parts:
C1, C2, C7: 22uF; C_0805_2012Metric
C3, C4, C5, C8, C10, C13: 100nF; C_0805_2012Metric
C6: 1uF; C_0805_2012Metric
C9, C12: 10uF; C_0805_2012Metric
C11: 470uF DNP; CP_Radial_D6.3mm_P2.50mm; not fitted
D1: 5V PWR; LED_0805_2012Metric
D2: STATUS; LED_0805_2012Metric
J1: USB-C USB2 sink; USB_C_Receptacle_HRO_TYPE-C-31-M-12
J2: EXT 5V IN; TerminalBlock_MaiXu_MX126-5.0-02P_1x02_P5.00mm
J4: microSD SPI; microSD_HC_Molex_104031-0811
J6: SPI EXP; PinHeader_1x08_P2.54mm_Vertical
J7: I2C EXP; PinHeader_1x04_P2.54mm_Vertical
J8: GPIO EXP; PinHeader_1x12_P2.54mm_Vertical
JP1: 5V source select; PinHeader_1x03_P2.54mm_Vertical
Q1, Q2: SS8050/MMBT3904; SOT-23
Q3: MMBT3904; SOT-23
R1, R2: 5.1k; R_0805_2012Metric
R3: 2.2k; R_0805_2012Metric
R4, R5, R6, R7, R14, R15, R16, R17, R18, R24: 10k; R_0805_2012Metric
R10: 1k; R_0805_2012Metric
R11, R12, R13: 22R; R_0805_2012Metric
R19, R20: 4.7k; R_0805_2012Metric
R25: 100k; R_0805_2012Metric
SJ1: GPIO2 LED EN; SolderJumper-2_P1.3mm_Open_TrianglePad1.0x1.5mm
SW1: EN/RST; SW_SPST_TL3342
SW2: BOOT; SW_SPST_TL3342
TP1: 5V_SYS; TestPoint_Pad_D1.5mm
TP2: 3V3; TestPoint_Pad_D1.5mm
TP3: GND; TestPoint_Pad_D1.5mm
TP4: EN; TestPoint_Pad_D1.5mm
TP5: BOOT; TestPoint_Pad_D1.5mm
TP6: UART0_TX; TestPoint_Pad_D1.5mm
TP7: UART0_RX; TestPoint_Pad_D1.5mm
TP8: GPIO32; TestPoint_Pad_D1.5mm
TP9: GPIO33; TestPoint_Pad_D1.5mm
TP10: SD_SCK; TestPoint_Pad_D1.5mm
TP11: SD_MOSI; TestPoint_Pad_D1.5mm
TP12: SD_MISO; TestPoint_Pad_D1.5mm
TP13: SD_CS; TestPoint_Pad_D1.5mm
TP14: I2S_BCLK; TestPoint_Pad_D1.5mm
TP15: I2S_WS; TestPoint_Pad_D1.5mm
TP16: I2S_DOUT; TestPoint_Pad_D1.5mm
TP17: AMP_MUTE_CTL; TestPoint_Pad_D1.5mm
TP18: AMP_SD_MODE; TestPoint_Pad_D1.5mm
U1: CH340C; SOIC-16_3.9x9.9mm_P1.27mm
U2: AP2112K-3.3; SOT-23-5
U3: ESP32-WROOM-32E
U4: MAX98357A blue module; PinHeader_1x07_P2.54mm_Vertical

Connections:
/3V3: C2.1, C3.1, C4.1, C5.1, C7.1, C8.1, C9.1, C10.1, J4.4 (VDD), J6.1, J7.2, J8.1, R6.1, R7.1, R14.1, R15.1, R16.1, R17.1, R18.1, R19.1, R20.1, TP2.1 (TP_1), U1.4 (V3), U1.16 (VCC), U2.5 (VOUT), U3.2 (3V3)
/5V_SYS: C1.1, C11.1, C12.1, C13.1, J6.8, J8.2, JP1.2 (COM1), R3.1, TP1.1 (TP_1), U2.1 (VIN), U2.3 (EN), U4.7 (VIN); also elsewhere on the board
/AMP_MUTE_BASE: Q3.1 (B), R24.2, R25.1
/AMP_MUTE_CTL: R24.1, TP17.1 (TP_1), U3.33 (GPIO21)
/AMP_SD_MODE: Q3.3 (C), TP18.1 (TP_1), U4.5 (SD/MODE)
/AUTO_BOOT_NODE: Q1.2 (E), Q2.3 (C)
/AUTO_DTR_B: Q1.1 (B), R4.2
/AUTO_RTS_B: Q2.1 (B), R5.2
/BOOT: Q2.2 (E), R7.2, SW2.1 (A), TP5.1 (TP_1), U3.25 (GPIO0)
/EN: C6.1, Q1.3 (C), R6.2, SW1.1 (A), TP4.1 (TP_1), U3.3 (EN)
/ESP_SD_CS: R13.1, U3.29 (GPIO5)
/ESP_SD_MOSI: R12.1, U3.37 (GPIO23)
/ESP_SD_SCK: R11.1, U3.30 (GPIO18)
/EXT_5V: J2.1, JP1.3 (B1)
/GND: C1.2, C2.2, C3.2, C4.2, C5.2, C6.2, C7.2, C8.2, C9.2, C10.2, C11.2, C12.2, C13.2, D1.2 (K), D2.2 (K), J1.A1 (GND), J1.A12 (GND), J1.B1 (GND), J1.B12 (GND), J1.SH (SHIELD), J2.2, J4.6 (VSS), J4.SH (SHIELD), J6.2, J7.1, J8.3, Q3.2 (E), R1.2, R2.2, R25.2, SW1.2 (B), SW2.2 (B), TP3.1 (TP_1), U1.1 (GND), U1.15 (R232), U2.2 (GND), U3.1 (GND1), U3.15 (GND2), U3.38 (GND3), U3.39 (P_GND), U4.6 (GND); also elsewhere on the board
/GPIO2_LED: SJ1.1 (A), U3.24 (GPIO2); also elsewhere on the board
/GPIO4: J8.6, U3.26 (GPIO4)
/GPIO13: J8.7, U3.16 (GPIO13)
/GPIO15: J8.8, U3.23 (GPIO15)
/GPIO32: J8.4, TP8.1 (TP_1), U3.8 (GPIO32)
/GPIO33: J8.5, TP9.1 (TP_1), U3.9 (GPIO33)
/GPIO35: J8.9, U3.7 (GPIO35)
/GPIO36: J8.10, U3.4 (GPIO36/SENSOR_VP)
/GPIO39: J8.11, U3.5 (GPIO39/SENSOR_VN)
/I2C_SCL: J7.4, R20.2, U3.28 (GPIO17)
/I2C_SDA: J7.3, R19.2, U3.27 (GPIO16)
/I2S_BCLK: TP14.1 (TP_1), U3.11 (GPIO26), U4.2 (BCLK)
/I2S_DOUT: TP16.1 (TP_1), U3.36 (GPIO22), U4.3 (DIN)
/I2S_WS: TP15.1 (TP_1), U3.10 (GPIO25), U4.1 (LRC/WS)
/LED_5V_A: D1.1 (A), R3.2
/LED_STATUS_A: D2.1 (A), R10.2
/LED_STATUS_IN: R10.1, SJ1.2 (B); also elsewhere on the board
/SD_CD: J8.12, U3.6 (GPIO34)
/SD_CS: J4.2 (DAT3/CS), R13.2, R18.2, TP13.1 (TP_1)
/SD_D1_PU: J4.8 (DAT1), R16.2
/SD_D2_PU: J4.1 (DAT2), R17.2
/SD_MISO: J4.7 (DAT0/MISO), J6.5, R15.2, TP12.1 (TP_1), U3.31 (GPIO19)
/SD_MOSI: J4.3 (CMD/MOSI), J6.4, R12.2, R14.2, TP11.1 (TP_1)
/SD_SCK: J4.5 (CLK), J6.3, R11.2, TP10.1 (TP_1)
/SPI_CS1: J6.6, U3.12 (GPIO27)
/SPI_CS2: J6.7, U3.13 (GPIO14)
/UART0_RX: TP7.1 (TP_1), U1.2 (TXD), U3.34 (RXD0/GPIO3)
/UART0_TX: TP6.1 (TP_1), U1.3 (RXD), U3.35 (TXD0/GPIO1)
/USB_CC1: J1.A5 (CC1), R1.1
/USB_CC2: J1.B5 (CC2), R2.1
/USB_DN: J1.A7 (D-), J1.B7 (D-), U1.6 (UD-)
/USB_DP: J1.A6 (D+), J1.B6 (D+), U1.5 (UD+)
/USB_DTR: R4.1, U1.13 (DTR)
/USB_RTS: R5.1, U1.14 (RTS)
/USB_VBUS: J1.A4 (VBUS), J1.A9 (VBUS), J1.B4 (VBUS), J1.B9 (VBUS), JP1.1 (A1)

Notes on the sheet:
USB-C + 5V power entry
USB-UART + auto program/reset
ESP32-WROOM-32E core
microSD SPI
I2S audio amp
Expansion headers + test pads
USB-C is sink-only 5V. No USB-PD negotiation.
Auto-reset topology follows Espressif DevKitC DTR/RTS -> EN/GPIO0 behavior.
GPIO12 intentionally left unconnected: strap pin can break flash boot if pulled high.
Use one common GND. USB monitor and external PSU share ground.
